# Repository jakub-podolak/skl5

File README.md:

# SKL 5
### SKL 5 Cortex M0 Smartwatch - fifth of my smartwatches
You can find eagle files, codes, stl's and images of my smartwatch

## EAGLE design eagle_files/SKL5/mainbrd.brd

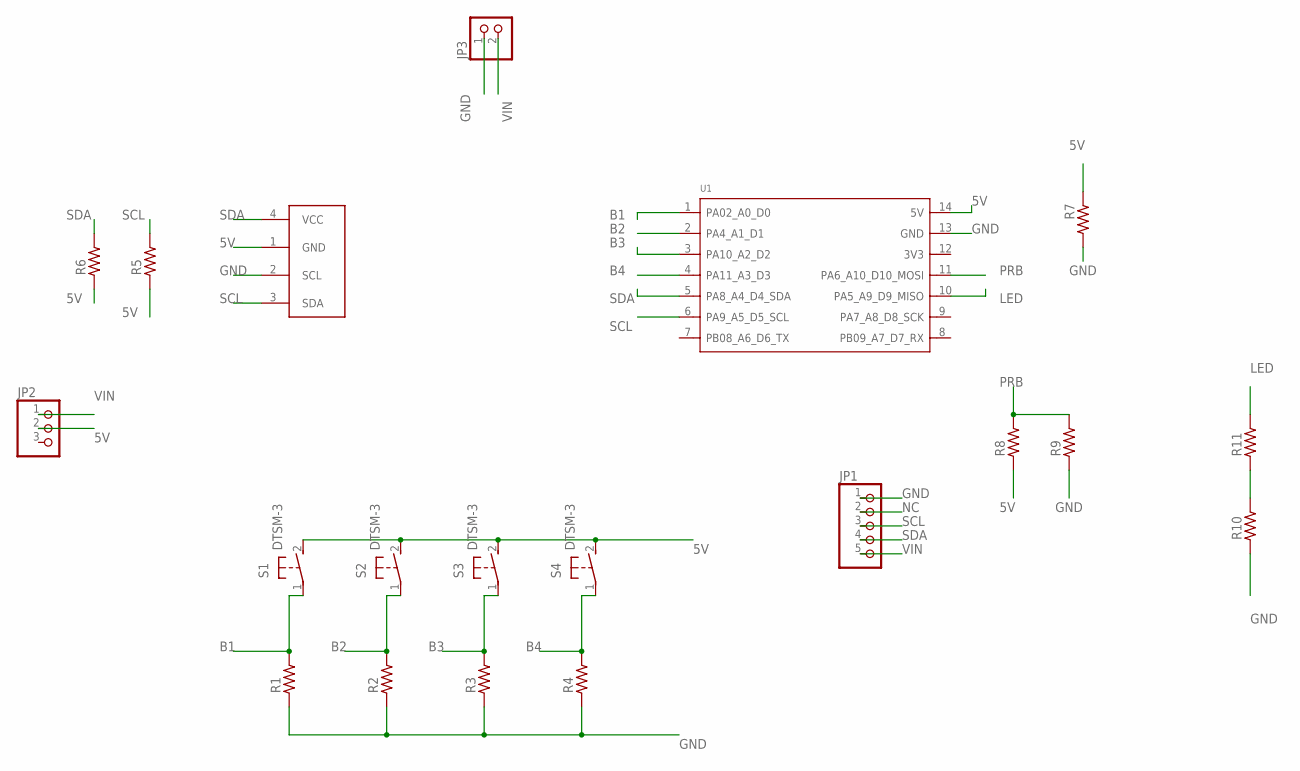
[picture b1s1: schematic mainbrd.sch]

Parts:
JP1: PINHD-1X5; 1X05
JP2: PINHD-1X3; 1X03
JP3: PINHD-1X2; 1X02
R1, R2, R3, R4, R5, R6, R7, R8, R9, R10, R11: R_1206; R1206
S1, S2, S3, S4: DTSM-3
U1: MOUDLE-SEEEDUINO-XIAO; MOUDLE14P-2.54-21X17.8MM
U$1: I2C_OLED; I2C_OLED_PACKAGE

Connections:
5V: JP2.2, R5.1, R6.1, R7.2, R8.1, S1.2, S2.2, S3.2, S4.2, U1.14 (5V), U$1.1 (GND)
B1: R1.2, S1.1, U1.1 (PA02_A0_D0)
B2: R2.2, S2.1, U1.2 (PA4_A1_D1)
B3: R3.2, S3.1, U1.3 (PA10_A2_D2)
B4: R4.2, S4.1, U1.4 (PA11_A3_D3)
GND: JP1.1, JP3.1, R1.1, R2.1, R3.1, R4.1, R7.1, R9.1, R10.1, U1.13 (GND), U$1.2 (SCL)
LED: R11.2, U1.10 (PA5_A9_D9_MISO)
unnamed: R10.2, R11.1
NC: JP1.2
PRB: R8.2, R9.2, U1.11 (PA6_A10_D10_MOSI)
SCL: JP1.3, R5.2, U1.6 (PA9_A5_D5_SCL), U$1.3 (SDA)
SDA: JP1.4, R6.2, U1.5 (PA8_A4_D4_SDA), U$1.4 (VCC)
VIN: JP1.5, JP2.1, JP3.2

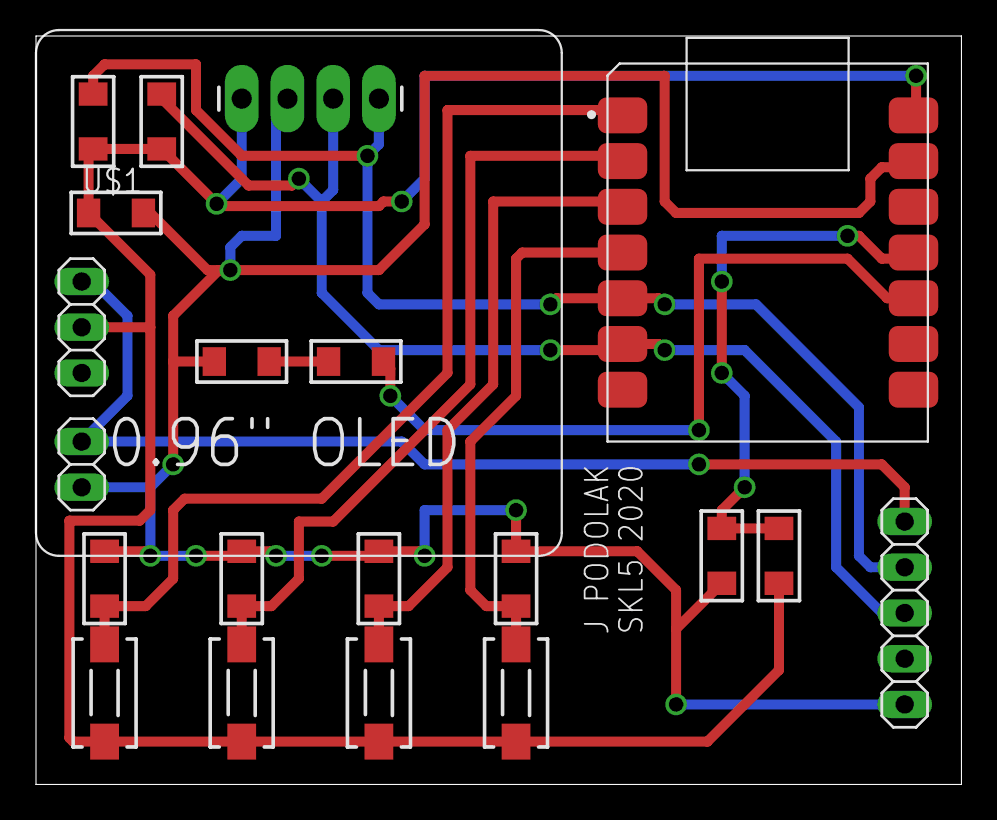
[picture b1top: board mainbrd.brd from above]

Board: 2 copper layers, 51.4 x 41.6 mm, 20 parts (0 on the bottom side), 12 nets.

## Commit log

2020-09-15 add first eagle files
2020-09-15 more thin on the left
2020-09-15 thicker bois
2020-09-15 fixes
2020-09-15 oled fixed lolz

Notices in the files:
parts and their libraries:
rc-master-smd: Copyright (C) 2007, Bob Starr
